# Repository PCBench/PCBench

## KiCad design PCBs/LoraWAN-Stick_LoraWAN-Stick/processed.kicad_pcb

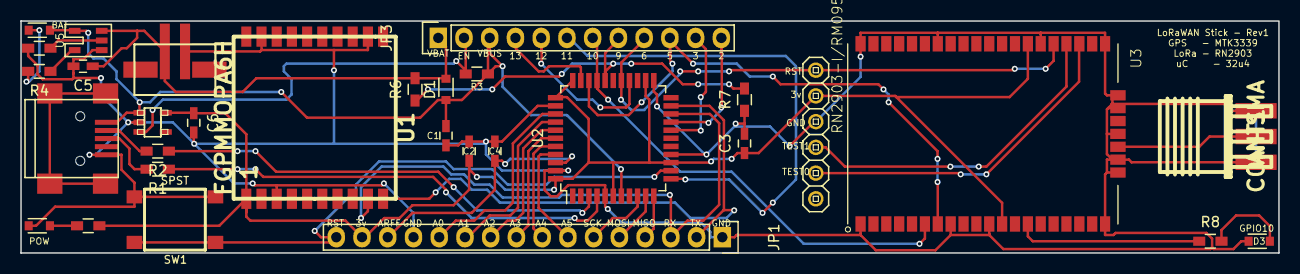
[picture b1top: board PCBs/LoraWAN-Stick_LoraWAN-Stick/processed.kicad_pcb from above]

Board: 2 copper layers, 124.2 x 22.9 mm, 31 parts (0 on the bottom side), 40 nets.

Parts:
ANT1: CON-SMA; CON-SMA-EDGE
C1, C2, C5, C6: 10uF; C_0603_HandSoldering
C3, C4: 1uF; C_0603_HandSoldering
CN1: JST_2PIN-SMT; adafruit-JST-PH-2-SMT
D1: DIODESCH; D_0805
D2: LED-BAT; D_0805
D3: LED-RED; D_0805
D4: LED-POW; D_0805
JP1: CONN_01X16; Pin_Header_Straight_1x16
JP2: PINHD-1X6; adafruit-1X06
JP3: PINHD-1X12; Pin_Header_Straight_1x12
P1: USB_OTG; USB_Mini-B
R1, R2: 22; R_0603_HandSoldering
R3, R6, R7: 100k; R_0603_HandSoldering
R4, R8, R9: 1k; R_0603_HandSoldering
R5: 10k; R_0603_HandSoldering
SW1: SPST; SW_PUSH_SMD
U1: FGPMMOPA6H
U2: ATmega32U4-AU; TQFP-44_10x10mm_Pitch0.8mm
U3: RN2903-I/RM095; XCVR_RN2903-I%2fRM095
U4: SPX3819
U5: MCP73831

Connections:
3v3: C2.1, C3.1, C6.1, JP1.15, JP2.2, R9.1, U1.1, U2.6, U2.14, U2.24, U2.33, U2.34, U2.44, U3.12, U3.34, U4.4
9: JP3.8, R6.1, R7.2, U2.29
/0: JP1.3, U1.9, U2.20
/1: JP1.2, U1.10, U2.21
/2: JP3.12, U2.19
/3: JP3.11, U2.18
/5: JP3.10, U2.31, U3.7
/6: JP2.1, JP3.9, U2.27, U3.32
/10: JP3.7, U2.30, U3.6
/11: JP3.6, U2.12
/12: JP3.5, U2.26
/13: JP3.4, U2.32
/A0: JP1.12, U2.36
/A1: JP1.11, U2.37
/A2: JP1.10, U2.38
/A3: JP1.9, U2.39
/A4: JP1.8, U2.40
/A5: JP1.7, U2.41
/EN: JP3.2, R3.1, U4.3
/MISO: JP1.4, U2.11
/MOSI: JP1.5, U2.10
/SCK: JP1.6, U2.9
/TEST0: JP2.5, U3.30
/TEST1: JP2.4, U3.31
ARFF: C4.1, JP1.14, U2.42
GND: ANT1.2, ANT1.3, ANT1.4, ANT1.5, C1.2, C2.2, C3.2, C4.2, C5.2, C6.2, CN1.1, D3.1, D4.1, JP1.1, JP1.13, JP2.3, P1.5, R5.1, R7.1, SW1.2, U1.3, U1.12, U1.19, U2.5, U2.15, U2.23, U2.35, U2.43, U3.1, U3.8, U3.11, U3.20, U3.21, U3.22, U3.24, U3.26, U3.27, U3.28, U3.33, U3.41, U3.47, U4.2, U5.2
unnamed: ANT1.1, U3.23
unnamed: D2.1, R4.2
unnamed: D3.2, R8.2
unnamed: D4.2, R9.2
unnamed: P1.2, R2.2
unnamed: P1.3, R1.2
unnamed: R1.1, U2.4
unnamed: R2.1, U2.3
unnamed: R4.1, U5.1
unnamed: R5.2, U5.5
unnamed: R8.1, U3.14
RST: JP1.16, SW1.1, U2.13
VBAT: C5.1, CN1.2, D1.1, JP3.1, R6.2, U5.3
VBUS: C1.1, D1.2, D2.2, JP3.3, P1.1, R3.2, U2.7, U4.1, U5.4

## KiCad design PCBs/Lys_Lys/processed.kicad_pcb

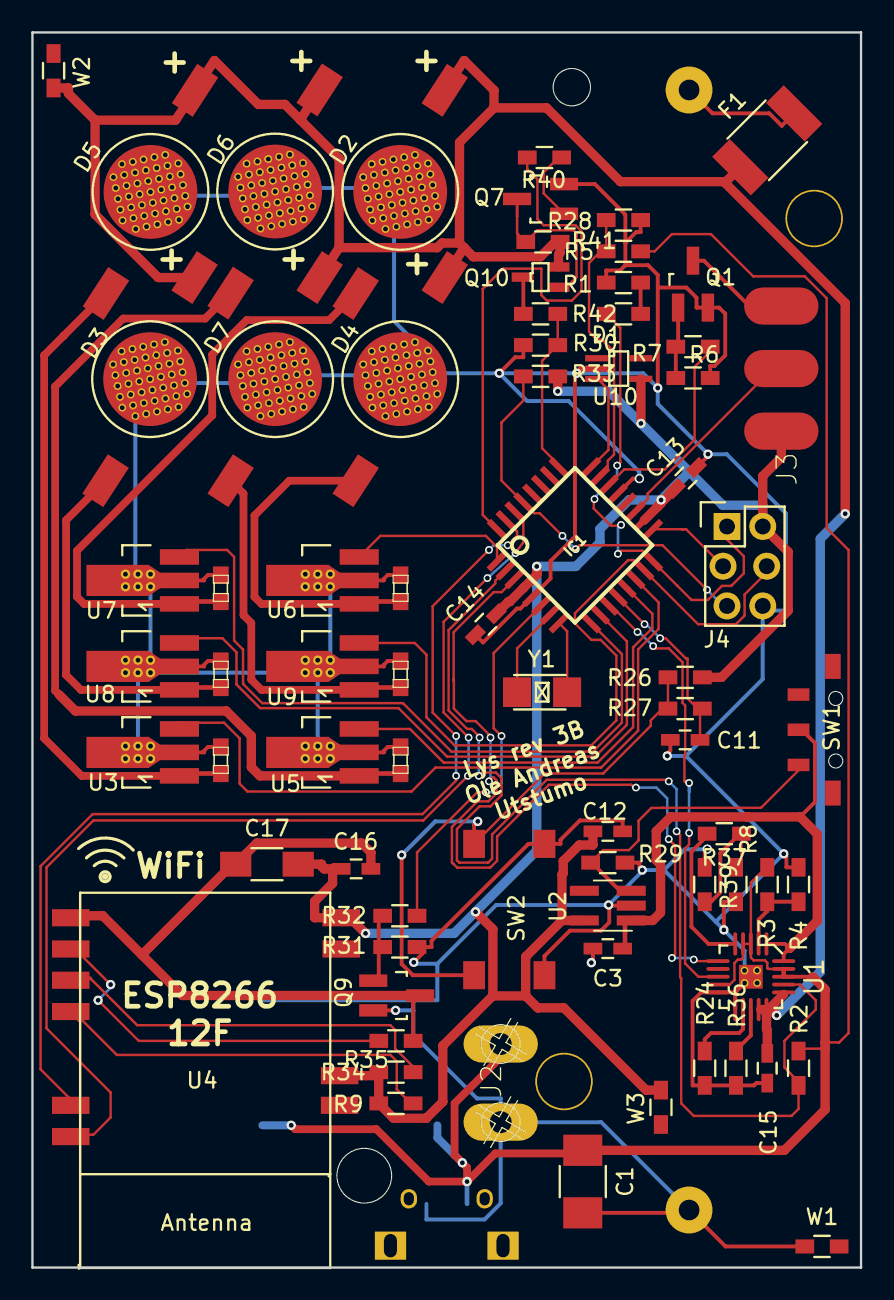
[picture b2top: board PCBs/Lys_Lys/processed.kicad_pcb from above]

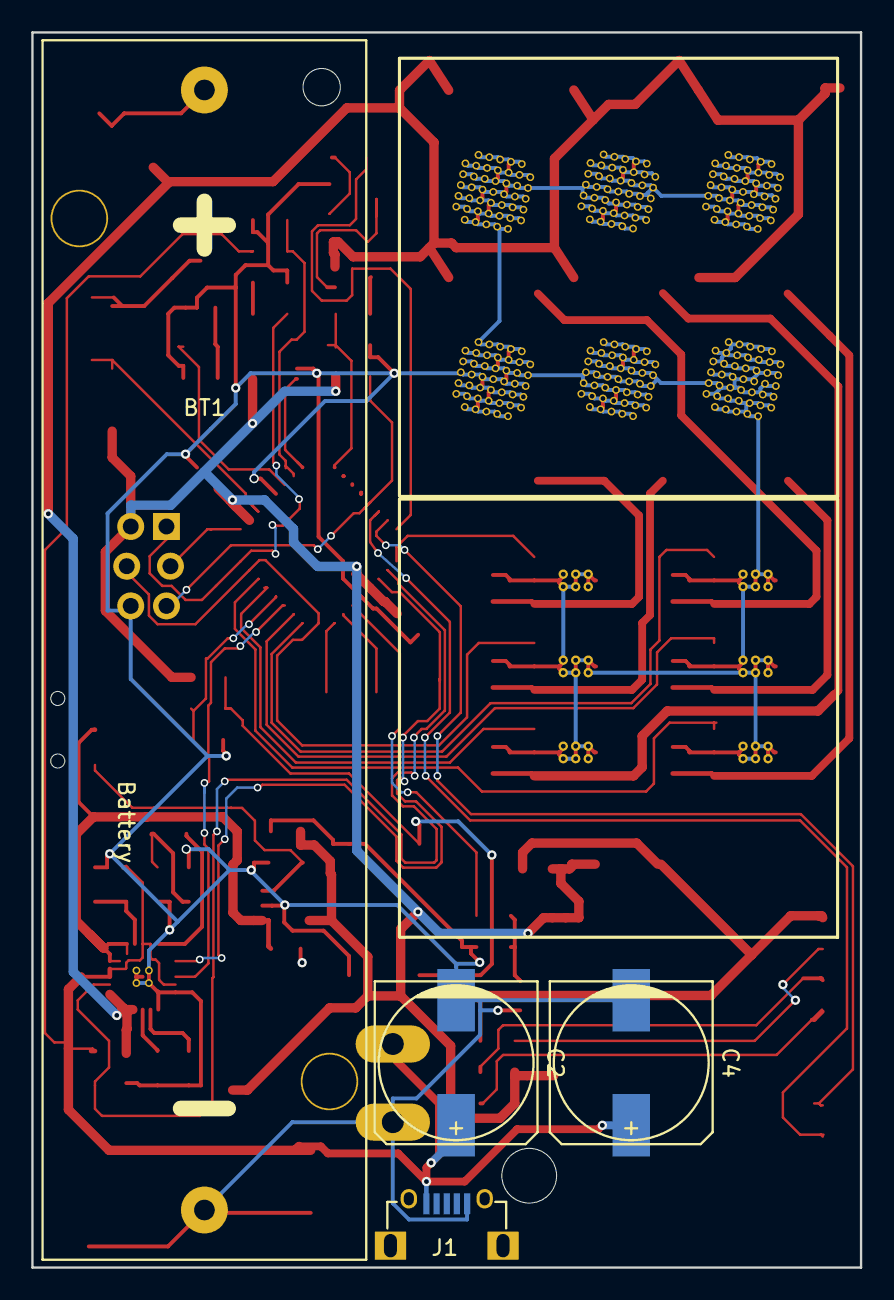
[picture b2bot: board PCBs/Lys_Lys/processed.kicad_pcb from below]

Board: 2 copper layers, 53.0 x 79.0 mm, 77 parts (4 on the bottom side), 54 nets.

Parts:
BT1: Battery; Keystone_1043_1860_holder
C1: 0.1u; C_1210_HandSoldering
C2, C4: CAPACITOR_POL-CASE_A; c_elec_10x10
C3, C15: 0.1u; C_0603_HandSoldering
C5, C6, C7, C8, C9, C10: C; dp_devices-C603
C11, C13, C14, C16: 0.1uF; C_0603_HandSoldering
C12: 1uF; C_0603_HandSoldering
C17: 10uF; C_1206_HandSoldering
D1: LED; R_0603_HandSoldering
D2, D3, D4, D5, D6, D7: LED; 1W_LED_bead_1
F1: FUSE; R_1812
IC1: ATMEGA168PB-AU; TQFP32-7x7
J1: USBJACK_micro; Multicomp_MC001009_handsolder
J2: CON_TERMINAL_BLOCK_02-5MM; Wire_terminal_x2
J3: CON_HEADER_1X03-PTH; Wire_Solder_Pads_x3_SMD
J4: CON_HEADER_2X03-PTH; SPI_Header_SnapIn
Q1, Q9: TSM2306; SOT-23_Handsoldering
Q7: PBSS4120T; SOT-23_Handsoldering
Q10: NX3008PBKW; SOT-323_handsoldering
R1, R5, R26, R28, R30, R33, R40, R41, R42: 10k; R_0603_HandSoldering
R2, R3, R4: 27k; R_0603_HandSoldering
R6, R31: 100k; R_0603_HandSoldering
R7, R27, R32: 200; R_0603_HandSoldering
R8, R24, R36, R37, R39: 6.8k; R_0603_HandSoldering
R9, R34, R35: 1k; R_0603_HandSoldering
R29: 1M; R_0603_HandSoldering
SW1: SPST; JS102000SAQN
SW2: SW_PUSH; MC32882
U1: MCP73871; QFN_20
U2: TLV733; SOT-23-5_Handsolder
U3, U5, U6, U7, U8, U9: AMC7135; SOT89-3_ThermalVias_Handsoldering
U4: ESP-12E; ESP8266_12F_handsolder
U10: MCP9700; SC-70-5_handsoldering
W1, W2, W3: TEST_1P; R_0603_HandSoldering
Y1: ABS25-32.768KHZ-6-T; ABS07-32.768KHZ-T

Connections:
+BATT: C15.1, D2.2, D3.2, D4.2, D5.2, D6.2, D7.2, F1.1, Q10.2, R41.1, U1.14, U1.15, U1.16, W2.1
ADC_EXT2: IC1.19, J3.2
ADC_batt: IC1.25, R30.1, R42.2
ADC_solar: IC1.23, R5.1, R28.2
ADC_temp: IC1.24, U10.3
BUTTON: C11.2, IC1.12, R27.1
Battsense_EN: IC1.32, R40.1
Chg_STAT1: IC1.11, U1.8
Chg_en: IC1.2, R2.1, U1.17
Chg_nPG: IC1.3, U1.6
ESP_RX: IC1.31, U4.21
ESP_TX: IC1.30, U4.22
ESP_en: IC1.6, R32.1
EXT_en: IC1.22, R7.1
GND: BT1.2, C1.2, C2.2, C4.2, C5.2, C6.2, C7.2, C8.2, C9.2, C10.2, C11.1, C12.2, C13.1, C14.1, C15.2, D2.0, D3.0, D4.0, D5.0, D6.0, D7.0, IC1.5, IC1.21, J1.5, J2.1, J4.6, Q1.2, Q7.2, Q9.2, R1.2, R4.1, R6.1, R8.1, R24.1, R28.1, R29.1, R30.2, R31.1, R36.1, R39.1, SW2.2, U1.0, U1.10, U1.11, U1.EP, U2.2, U3.0, U3.2, U5.0, U5.2, U6.0, U6.2, U7.0, U7.2, U8.0, U8.2, U9.0, U9.2, U10.2, W1.1
MISO: D1.2, IC1.16, J4.1
MOSI: IC1.15, J4.4, U9.3
unnamed: BT1.1, F1.2
unnamed: C5.1, D5.1, U3.1
unnamed: C6.1, D6.1, U5.1
unnamed: C7.1, D4.1, U6.1
unnamed: C8.1, D2.1, U7.1
unnamed: C9.1, D3.1, U8.1
unnamed: C10.1, D7.1, U9.1
unnamed: C16.1, C17.1, Q9.3, R35.1, U4.15
unnamed: D1.1, R1.1
unnamed: J3.3, Q1.3
unnamed: Q1.1, R6.2, R7.2
unnamed: Q7.1, R40.2
unnamed: Q9.1, R31.2, R32.2
unnamed: Q7.3, Q10.1, R41.2
unnamed: Q10.3, R42.1
unnamed: R3.1, R4.2, U1.2
unnamed: R9.2, U4.18
unnamed: R24.2, U1.12
unnamed: R26.1, R27.2, SW2.1
unnamed: R29.2, SW1.1, U2.3
unnamed: R34.2, U4.17
unnamed: R35.2, U4.16
unnamed: R36.2, U1.13
unnamed: R37.1, U1.5
unnamed: R8.2, R37.2, R39.2
PWM_LED1: IC1.9, U7.3
PWM_LED2: IC1.13, U5.3
PWM_LED3: IC1.14, U3.3
PWM_LED4: IC1.1, U6.3
PWM_LED5: IC1.10, U8.3
SCK: IC1.17, J4.3
VCC: C12.1, C13.2, C14.2, C16.2, C17.2, IC1.4, IC1.18, J3.1, J4.2, R9.1, R26.2, R33.1, R34.1, U2.5, U4.3, U4.8, U10.4, W3.1
VDD: SW1.2, U1.1, U1.20, U2.1
VPP: C1.1, C2.1, C4.1, J1.1, J2.2, R2.2, R3.2, R5.2, U1.3, U1.4, U1.9, U1.18, U1.19
XTAL1: IC1.7, Y1.1
XTAL2: IC1.8, Y1.2
nRESET: IC1.29, J4.5, R33.2

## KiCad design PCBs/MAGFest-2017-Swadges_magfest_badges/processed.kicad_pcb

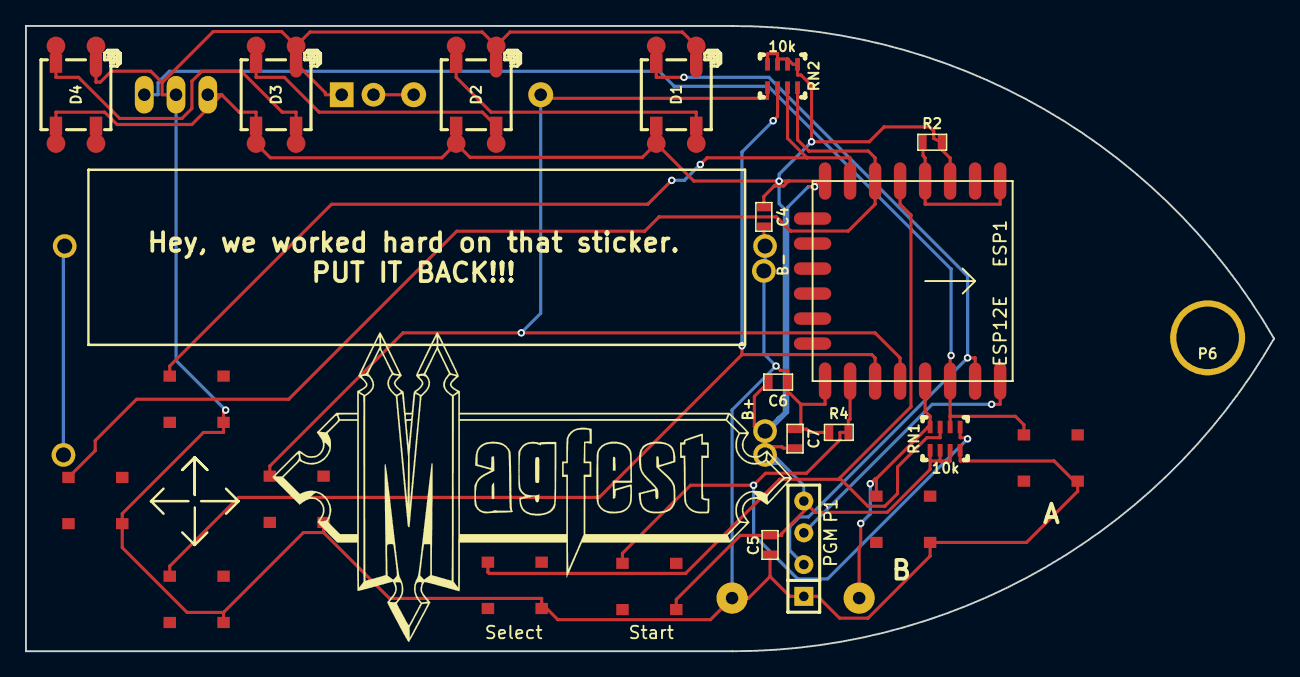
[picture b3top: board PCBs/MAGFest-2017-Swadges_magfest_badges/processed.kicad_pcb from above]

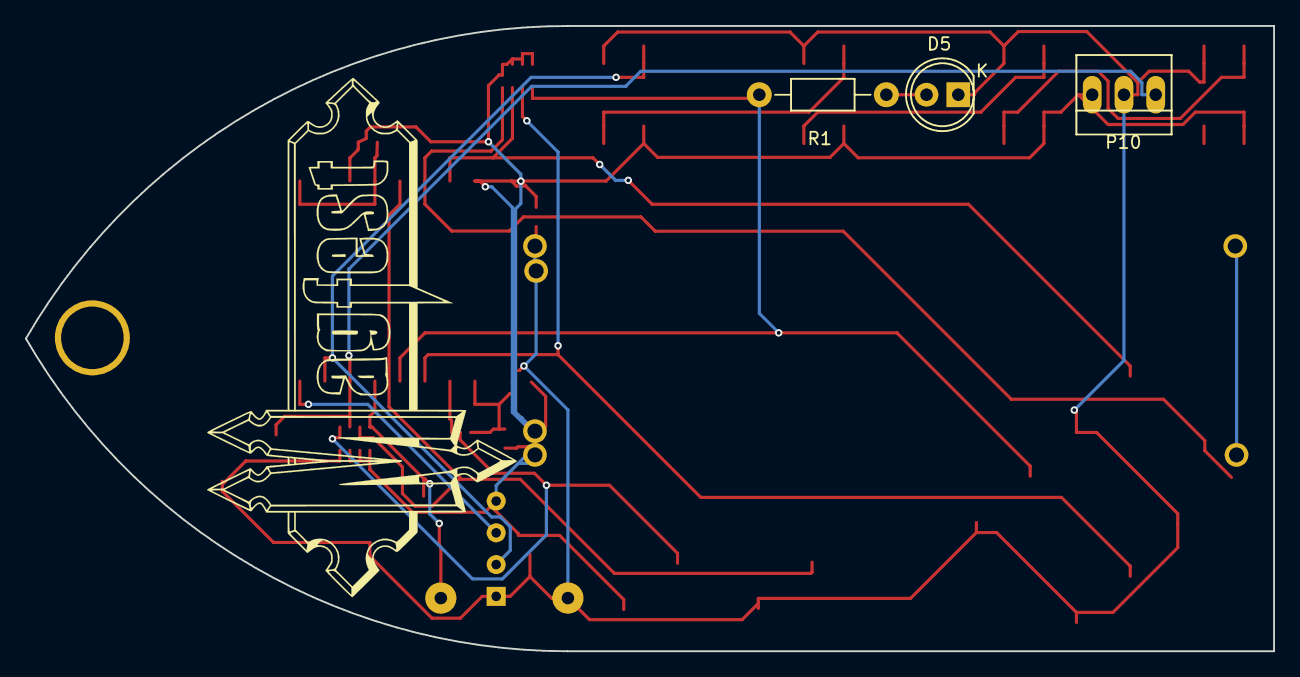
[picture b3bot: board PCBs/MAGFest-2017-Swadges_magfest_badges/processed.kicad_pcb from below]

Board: 2 copper layers, 99.8 x 50.0 mm, 34 parts (5 on the bottom side), 18 nets.

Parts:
C4, C5: 10u; SM0603
C6, C7: .1u; SM0603
D1, D2, D3, D4: WS2812B; WS2812BQ
D5: LED; LED-5MM
ESP1: ESP12E
G1: LOGO; outline
P1: PGM; RECT_4x1
P3, P5: B+; SMTPIN
P4, P7: B-; SMTPIN
P6: HOLE_LANYARD; SMTPIN
P8, P9: 1.5; SMTPIN
P10: CONN_01X03; PINHEAD1-3
R1: R; Resistor_Horizontal_RM10mm
R2, R4: 12k; SM0603
RN1, RN2: 10k; NETWORK1206
SP1: SPEAKER; BUZZER
SW1, SW2, SW3, SW4, SW5, SW6, SW7, SW8: TACTILE

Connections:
+3V3: C4.1, C5.1, C6.1, C7.1, D1.1, D2.1, D3.1, D4.1, ESP1.3, ESP1.8, P1.4, P3.1, P5.1, P10.3, R2.2, RN1.5, RN1.6, RN1.7, RN2.5, RN2.6, RN2.7, RN2.8, SW5.4
GND: C4.2, C5.2, C6.2, C7.2, D1.3, D2.3, D3.3, D4.3, D5.1, ESP1.15, P1.1, P4.1, P7.1, P10.2, R4.2, RN1.8, SP1.2, SW1.4, SW2.4, SW3.4, SW4.4, SW6.4, SW7.4, SW8.4
GP0: ESP1.18, R1.2, RN2.1, SW2.1
GP2: ESP1.17, RN2.2, SW4.1
GP4: ESP1.19, RN1.4, SP1.1, SW3.1
GP5: ESP1.20, P10.1, RN1.2, SW1.1
GP12: ESP1.6, RN2.4, SW8.1
GP13: ESP1.7, RN2.3, SW6.1
GP14: ESP1.5, RN1.3, SW7.1
GP15: ESP1.16, R4.1, RN1.1, SW5.1
unnamed: D1.2, D2.4
unnamed: D2.2, D3.4
unnamed: D3.2, D4.4
unnamed: D5.2, R1.1
RESET: ESP1.1, ESP1.4, R2.1
URX: D1.4, ESP1.21, P1.2
UTX: ESP1.22, P1.3
V15: P8.1, P9.1

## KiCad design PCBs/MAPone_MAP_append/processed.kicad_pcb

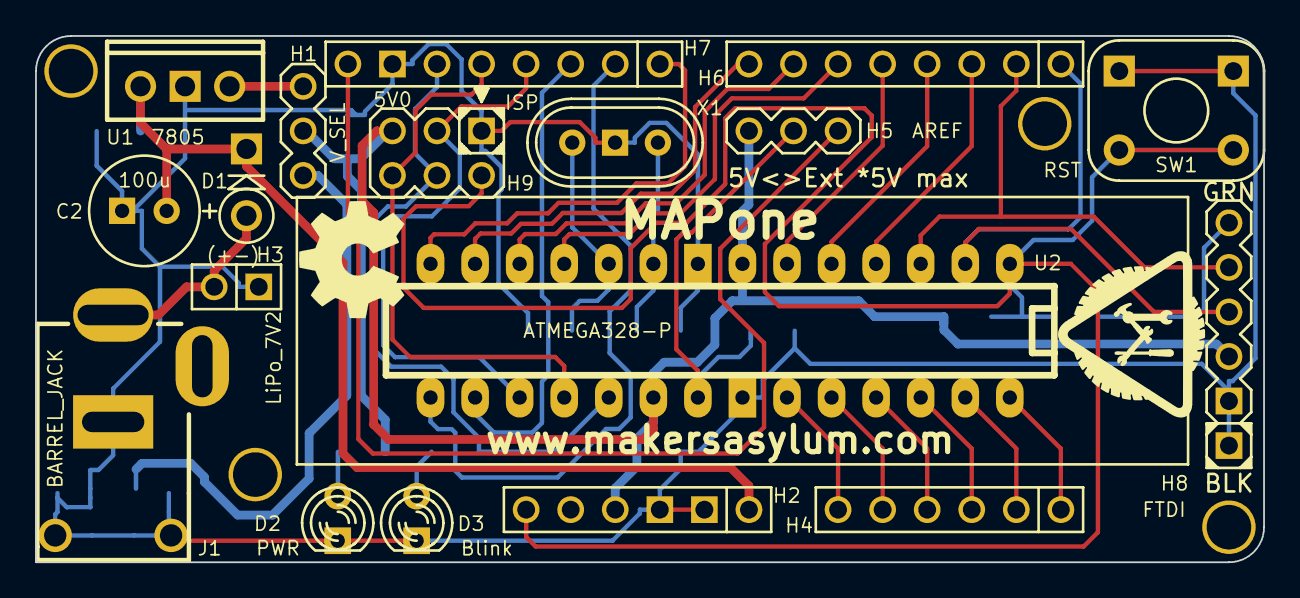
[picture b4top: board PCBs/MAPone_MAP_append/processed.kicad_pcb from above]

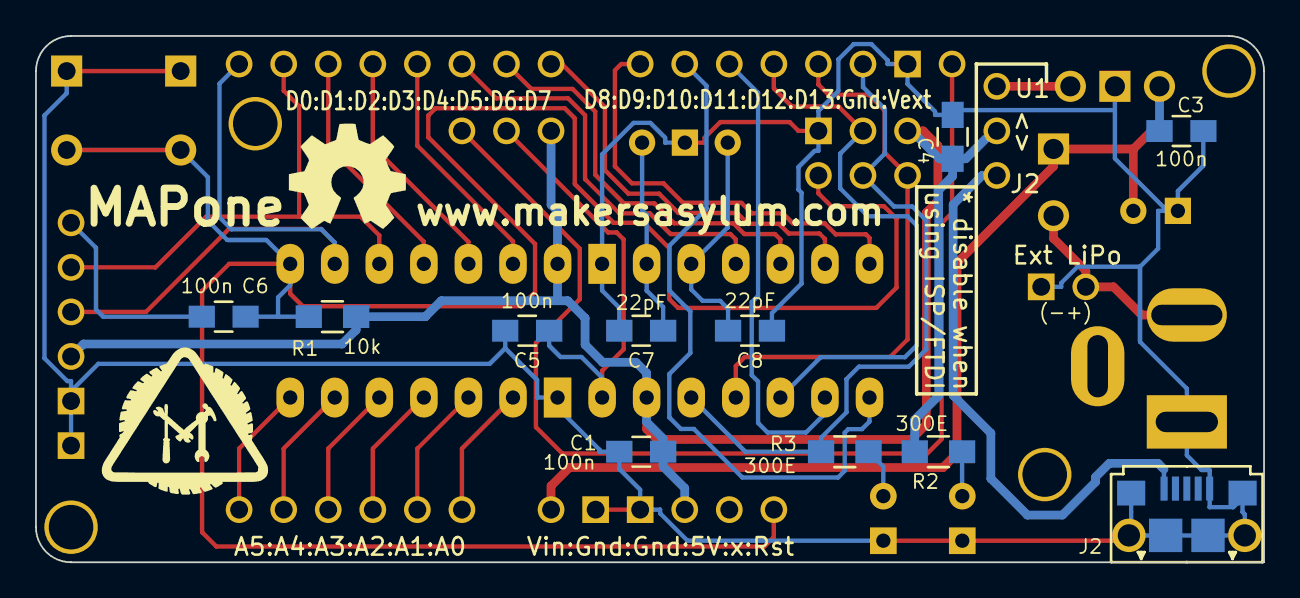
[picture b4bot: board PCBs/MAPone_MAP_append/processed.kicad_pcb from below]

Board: 2 copper layers, 70.0 x 30.0 mm, 37 parts (13 on the bottom side), 34 nets.

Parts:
C1, C3, C4, C5, C6: 100n; C_0805_HandSoldering
C2: 100u; Elko_vert_11.2x6.3mm_RM2.5
C7, C8: 22pF; C_0805_HandSoldering
D1: 1N4007; Diode_DO-41_SOD81_Vertical_KathodeUp
D2: PWR; LED-3MM
D3: Blink; LED-3MM
H1: V_SEL; Header_3
H2: Power; Socket_Strip_Straight_1x06
H3: LiPo_7V2; Pin_Header_Straight_1x02
H4: ANALOG; Socket_Strip_Straight_1x06
H5: AREF; Header_A_REF
H6: IO_L; Socket_Strip_Straight_1x08
H7: IO_H; Socket_Strip_Straight_1x08
H8: FTDI; Header_FTDI
H9: ISP; Header_ICSP
J1: BARREL_JACK; JACK_ALIM
J2: USB-Micro; USB_B_Micro
P1, P2, P3, P4: CONN_1; vite_3mm
R1: 10k; R_0805_HandSoldering
R2, R3: 300E; R_0805_HandSoldering
SW1: RST; SW-PB
U1: 7805; LM78XXV
U2: ATMEGA328-P; DIP-28__300_ELL_ZIF
X1: 16MHz; Crystal_HC49-U_Vertical_3Pin
Z1, Z2: CONN_1; MA_Logo2
Z6, Z7: CONN_1; OSHW_6mm

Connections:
/5V: C1.1, C4.1, H1.2, H2.4, H5.1, H8.3, H9.2, R1.1, R2.2, U2.7, U2.20
/AD0: H4.6, U2.23
/AD1: H4.5, U2.24
/AD2: H4.4, U2.25
/AD3: H4.3, U2.26
/AD4_SDA: H4.2, U2.27
/AD5_SCL: H4.1, U2.28
/AREF: C5.1, H5.2, U2.21
/MISO: H7.5, H9.1, U2.18
/MOSI_P: H7.4, H9.4, U2.17
/PB0: H7.1, U2.14
/PB1_P: H7.2, U2.15
/PD2: H6.3, U2.4
/PD3_P: H6.4, U2.5
/PD4: H6.5, U2.6
/PD5_P: H6.6, U2.11
/PD6_P: H6.7, U2.12
/PD7: H6.8, U2.13
/RST: C6.1, H2.6, H9.5, R1.2, SW1.2, U2.1
/RXD: H6.1, H8.4, U2.2
/SCK: H7.6, H9.3, R3.1, U2.19
/SS_P: H7.3, U2.16
/TXD: H6.2, H8.5, U2.3
/V_IN: C2.1, C3.2, D1.2, H2.1, U1.VI
/V_REG: H1.1, U1.VO
/V_USB: H1.3, J2.1
/Vext: H5.3, H7.8
GND: C1.2, C2.2, C3.1, C4.2, C5.2, C7.2, C8.2, D2.2, D3.2, H2.2, H2.3, H3.1, H7.7, H8.1, H8.2, H9.6, J1.2, J2.5, J2.T1, J2.T2, J2.T3, J2.T4, J2.T5, J2.T6, SW1.1, U1.GND, U2.8, U2.22, X1.3
unnamed: C6.2, H8.6
unnamed: C7.1, U2.9, X1.1
unnamed: C8.1, U2.10, X1.2
unnamed: D1.1, H3.2, J1.1
unnamed: D2.1, R2.1
unnamed: D3.1, R3.2

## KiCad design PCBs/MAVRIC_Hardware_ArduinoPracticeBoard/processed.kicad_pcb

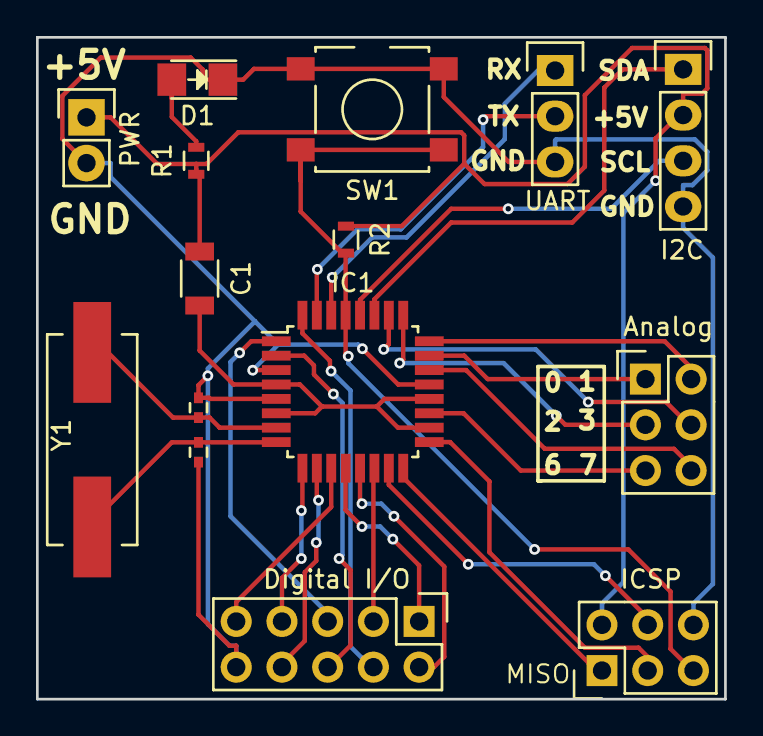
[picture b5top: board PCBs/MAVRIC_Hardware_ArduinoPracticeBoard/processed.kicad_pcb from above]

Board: 2 copper layers, 38.2 x 36.8 mm, 15 parts (0 on the bottom side), 29 nets.

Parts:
Analog: Analog; Pin_Header_Straight_2x03
C1: 10u; C_1206
CXtalIn1: 18pf; C_0402
CXtalout1: 18pf; C_0402
D1: LED; LED_1206
Digital I/O: Digital; Pin_Header_Straight_2x05
I2C: I2C; Pin_Header_Straight_1x04
IC1: ATMEGA328-A; TQFP-32_7x7mm_Pitch0.8mm
ICSP: ICSP; Pin_Header_Straight_2x03
PWR: Power; Pin_Header_Straight_1x02
R1: <10k; R_0603
R2: 10k; R_0603
SW1: SPST; SW_SPST_B3S-1100
UART: UART; Pin_Header_Straight_1x03
Y1: 16MHz; Crystal_HC49-SD_SMD

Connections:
+5V: C1.1, I2C.2, ICSP.2, PWR.1, R1.1, R2.1
/ADC0: Analog.1, IC1.23
/ADC1: Analog.2, IC1.24
/ADC2: Analog.3, IC1.25
/ADC3: Analog.4, IC1.26
/ADC6: Analog.5, IC1.19
/ADC7: Analog.6, IC1.22
/MISO: IC1.16, ICSP.1
/MOSI: IC1.15, ICSP.4
/OSC1: CXtalIn1.2, IC1.7, Y1.2
/OSC2: CXtalout1.2, IC1.8, Y1.1
/PB0: Digital I/O.1, IC1.12
/PB1: Digital I/O.2, IC1.13
/PB2: Digital I/O.3, IC1.14
/PD2: Digital I/O.4, IC1.32
/PD3: Digital I/O.5, IC1.1
/PD4: Digital I/O.6, IC1.2
/PD5: Digital I/O.7, IC1.9
/PD6: Digital I/O.8, IC1.10
/PD7: Digital I/O.9, IC1.11
/RST: IC1.29, ICSP.5, R2.2, SW1.1
/RX: IC1.30, UART.1
/SCK: IC1.17, ICSP.3
/SCL: I2C.3, IC1.28
/SDA: I2C.1, IC1.27
/TX: IC1.31, UART.2
GND: CXtalIn1.1, CXtalout1.1, D1.1, Digital I/O.10, I2C.4, IC1.3, IC1.5, IC1.21, ICSP.6, PWR.2, SW1.2, UART.3
unnamed: C1.2, IC1.4, IC1.6, IC1.18, IC1.20
unnamed: D1.2, R1.2
